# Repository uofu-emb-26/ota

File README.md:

# OTA Firmware Update Project

Reliable A/B firmware update foundation for STM32 with an ESP32 transport bridge.  
Here is the final presentation video showing a demo and explanation of everything in this readme:

## Demo Videos
https://youtu.be/UHACsZe9ke4  
https://youtube.com/shorts/yXXsLTlftgA?feature=share

## Table of Contents
* [Project Overview](#project-overview)
* [System Architecture](#system-architecture)
* [Hardware Interfaces & Wiring](#hardware-interfaces--wiring)
* [Basic Setup Instructions](#basic-setup-instructions)
* [Flowcharts](#flowcharts)
* [Current Implementation Status](#current-implementation-status)
* [Repository Layout](#repository-layout)
* [Authors](#authors)

## Project Overview

### Purpose
Many embedded products are deployed in places where physical reflashing is slow, costly, or impossible. A failed firmware update can also brick a device if there is no recovery path. This project builds a robust over-the-air (OTA) update pipeline for an STM32 platform to solve this problem.

### Functionality
The system utilizes an A/B swap firmware update layout. The design keeps one known-good binary active while writing a new downloaded binary to an inactive slot. This allows updates to be validated before they become permanent. The update download process is concurrent. Main application tasks are not halted while the new binary is fetched.

Key components:
* A custom STM32 bootloader validates candidate app binaries at boot.
* The same application is built twice into Slot A and Slot B with specific binary information.
* OTA update workflow metadata is stored in flash with power-fail-safe writes.
* An ESP32 transport companion delivers update payloads to the STM32 application over UART.

## System Architecture

End-to-end update path:
1. A new firmware binary file is delivered over the network to the ESP32 bridge (stored at https://github.com/anton2uha/OTAfiles).
2. HiveMQ sends a fetch request to the ESP32. The ESP32 downloads the binaries to its local flash.
3. The running STM32 application receives the payload from the ESP32 via UART and writes it to the dormant flash bank.
4. The application marks the dormant slot as pending and reboots.
5. The bootloader validates available slots (integrity, CRC) and selects the boot target with the highest version.
6. The new app image confirms itself after health checks.

### Architecture Diagrams

## Hardware Interfaces & Wiring
### Gerber files and kicad_pcb files can be found in the ``/hardware_design_resources`` dir, for those interested in ordering the hardware to run the OTA.
[//]: # ([PLACEHOLDER: Insert Wiring Diagram Here])

### ESP32 to STM32 UART Pinout
| ESP32 | STM32 |
|---|---|
| GPIO17 (TX) | RX pin (PC5) |
| GPIO16 (RX) | TX pin (PC4) |
| GND | GND |

### STM32 Interfaces
* `UART3`: OTA data path from ESP32 to STM32 (Pins PC4, PC5).
* `UART4`: Debug output path.

### ESP32 Interfaces
* `UART0`: USB serial to receive new programs via PlatformIO.
* `UART2`: Binary transfer path toward STM32 OTA updater.

## Basic Setup Instructions

### 1. ESP32 Bridge Setup
**Requirements:** VS Code with PlatformIO extension, HiveMQ Cloud account (free tier), and a 2.4GHz WiFi network.

1. Configure WiFi credentials in `ota_esp32/src/main.cpp`:
   ```cpp
   const char* ssid = "your_network";
   const char* password = "your_password";
   ```
2. Configure the server URL and MQTT credentials in `ota_esp32/src/main.cpp`:
   ```cpp
   #define MQTT_BROKER "your-cluster.hivemq.cloud"
   #define MQTT_USER   "your_username"
   #define MQTT_PASS   "your_password"
   ```
   Update the IP in `fetchBinary()` and `checkForUpdate()` to point to your hosted binaries.
3. Build and upload using PlatformIO. Ensure the ESP32 device is connected via USB. Note: If using WSL, ensure your user is in the `dialout` group to access `/dev/ttyUSB0`.

### 2. STM32 Firmware Setup
**Requirements:** CMake and ARM GCC toolchain.

1. Navigate to the `OTA` directory.
2. Run the following CMake commands to build the bootloader and the two application slots:
   ```bash
   cmake --preset Debug -B build/Debug
   cmake --build build/Debug --target OTA_bootloader
   cmake --build build/Debug --target OTA_app_a
   cmake --build build/Debug --target OTA_app_b
   ```
3. Flash the generated `.elf` or `.hex` files to the STM32 starting at address `0x08000000` for the bootloader.

## Flowcharts

### Bootloader FSM

### UART ESP32 to STM32 Protocol FSM

## Current Implementation Status

* Implemented A/B flash partitioning and custom bootloader runtime.
* Runtime slot probing with vector checks, manifest checks, CRC checks, and version comparison.
* Shared app source built into two linked images (Slot A and Slot B).
* Power-fail-safe metadata persistence with scratch-page journaling.
* STM32 app-side `UART3` framed OTA receive/write pipeline.
* ESP32 protocol bridge integration.

## Repository Layout

* `OTA`: STM32 firmware workspace.
* `OTA/README.md`: Technical details on file map, flash map, and build/flash details.
* `OTA/PROJECT_HANDOVER.md`: Detailed architecture and roadmap.
* `OTA/ota_esp32`: ESP32 companion workspace.

## Authors

* Sameeran Chandorkar
* Jeffrey Hansen
* Nick Baret
* Anthony Lesik

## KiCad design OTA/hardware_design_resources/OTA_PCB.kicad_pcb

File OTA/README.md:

# OTA STM32 Firmware Workspace

Technical implementation README for the firmware workspace in this directory.

## Table of Contents

- [Overview](#overview)
- [Current Boot Behavior](#current-boot-behavior)
- [Hardware + Interface Plan](#hardware--interface-plan)
- [Memory Layout](#memory-layout)
- [Code Organization](#code-organization)
- [Build and Artifacts](#build-and-artifacts)
- [Flash and Run](#flash-and-run)
- [Status and Roadmap](#status-and-roadmap)

## Overview

This workspace implements a software-managed `A/B OTA` foundation for `STM32F072xB`.

Core components:

- Custom bootloader at flash base.
- Single shared application codebase linked twice (`Slot A`, `Slot B`).
- Per-slot image manifest (`ota_image_info`) embedded in each app image.
- Metadata persistence (`ota_metadata`) for OTA workflow state.

## Current Boot Behavior

Bootloader uses metadata-driven trial/rollback policy. Image validity is still determined from the per-slot manifest.

Decision flow:

1. Probe `Slot A` and `Slot B` (vector table + manifest magic/format/size + CRC).
2. Read OTA metadata (falls back to safe defaults on blank/corrupted flash).
3. If a `pending_slot` is recorded in metadata:
   - If pending slot is invalid or `trial_boot_count >= OTA_MAX_TRIAL_BOOTS` → **rollback** to `confirmed_slot`.
   - Otherwise → increment `trial_boot_count`, persist metadata, **trial boot** pending slot.
4. If no `pending_slot` → boot the recorded `active_slot` if valid.
5. Fallback: version-based runtime selection if active slot is unavailable.
6. If no valid slot found → `BOOT_ERR_NO_VALID_SLOT`, bootloader loops.

Rollback mechanics:
- `ota_mark_slot_pending(slot)` called by the app after writing a new image to the dormant slot.
- App must call `ota_confirm_current_slot()` within `OTA_MAX_TRIAL_BOOTS` boots to promote the slot.
- If not confirmed in time, bootloader rolls back to the previous `confirmed_slot` on next reset.

Implementation references:

- [Core/Src/boot/bootloader_main.c](Core/Src/boot/bootloader_main.c)
- [Core/Src/boot/bootloader.c](Core/Src/boot/bootloader.c)
- [Core/Inc/common/ota_image_info.h](Core/Inc/common/ota_image_info.h)

## Hardware + Interface Plan

### STM32

- `UART3`: planned OTA payload ingress from ESP32 updater.
- `UART4`: debug output path.

### ESP32 companion

- `UART0`: planned binary transfer path toward STM32 app updater.
- `UART2`: planned debug output path.

Companion workspace:

- [ota_esp32](ota_esp32)

## Memory Layout

| Region | Start | End | Size |
|---|---|---|---|
| Bootloader | `0x08000000` | `0x08003FFF` | `16 KB` |
| Slot A | `0x08004000` | `0x080117FF` | `54 KB` |
| Slot B | `0x08011800` | `0x0801EFFF` | `54 KB` |
| Scratch | `0x0801F000` | `0x0801F7FF` | `2 KB` |
| Metadata | `0x0801F800` | `0x0801FFFF` | `2 KB` |

RAM note:

- Vector mirror reserved at `0x20000000` to `0x200000BF`.
- App linker scripts place RAM start at `0x20000100`.

Relevant definitions:

- [Core/Inc/boot/ota_config.h](Core/Inc/boot/ota_config.h)
- [STM32F072_BOOTLOADER.ld](STM32F072_BOOTLOADER.ld)
- [STM32F072_APP_A.ld](STM32F072_APP_A.ld)
- [STM32F072_APP_B.ld](STM32F072_APP_B.ld)

## Code Organization

### Bootloader

- [Core/Inc/boot/bootloader.h](Core/Inc/boot/bootloader.h): bootloader API.
- [Core/Src/boot/bootloader.c](Core/Src/boot/bootloader.c): slot probe, validation, selection, jump.
- [Core/Src/boot/bootloader_main.c](Core/Src/boot/bootloader_main.c): bootloader entrypoint.
- [Core/Src/boot/bootloader_it.c](Core/Src/boot/bootloader_it.c): bootloader interrupt handlers.

### Metadata + workflow state

- [Core/Inc/boot/ota_metadata.h](Core/Inc/boot/ota_metadata.h): metadata layout and API.
- [Core/Src/common/ota_metadata.c](Core/Src/common/ota_metadata.c): CRC, scratch-journal read/write, confirm/pending APIs.

### App image manifest + helpers

- [Core/Inc/common/ota_image_info.h](Core/Inc/common/ota_image_info.h)
- [Core/Src/common/ota_image_info.c](Core/Src/common/ota_image_info.c)
- [Core/Inc/common/ota_app_helper.h](Core/Inc/common/ota_app_helper.h)

### Flash programming abstraction

- [Core/Inc/common/flash_update.h](Core/Inc/common/flash_update.h)
- [Core/Src/common/flash_update.c](Core/Src/common/flash_update.c)

### App entry

- [Core/Src/app/main.c](Core/Src/app/main.c): startup sequence and `ota_confirm_current_slot()` call.

## Build and Artifacts

Primary targets:

- `OTA_bootloader`
- `OTA_app_a`
- `OTA_app_b`

Build commands:

```bash
cmake --preset Debug -B build/Debug
cmake --build build/Debug --target OTA_bootloader
cmake --build build/Debug --target OTA_app_a
cmake --build build/Debug --target OTA_app_b
```

Generated outputs:

- `*.elf`: debug + programming input.
- `*.bin`: raw image payload.
- `*.hex`: address-aware image.
- `*.map`: memory usage map.

Build configuration and post-build tools:

- [CMakeLists.txt](CMakeLists.txt)
- [tools/ota_patch_image_crc.py](tools/ota_patch_image_crc.py)

## Flash and Run

Workspace tasks include:

- `Build All Targets`
- `Flash Bootloader`
- `Flash App A`
- `Flash App B`
- `Flash All Targets`
- `Erase Flash`

Manual command references:

- [flash_commands.txt](flash_commands.txt)

## Status and Roadmap

Current implementation and milestones are tracked in:

- [PROJECT_HANDOVER.md](PROJECT_HANDOVER.md)

Near-term work:

1. Complete app-side `UART3` receive/write pipeline.
2. Complete dormant-slot update state machine.
3. Re-enable metadata-driven trial/rollback policy in bootloader.
4. Add stronger recovery UX for no-valid-slot cases.
5. Add authenticity and anti-rollback security features.

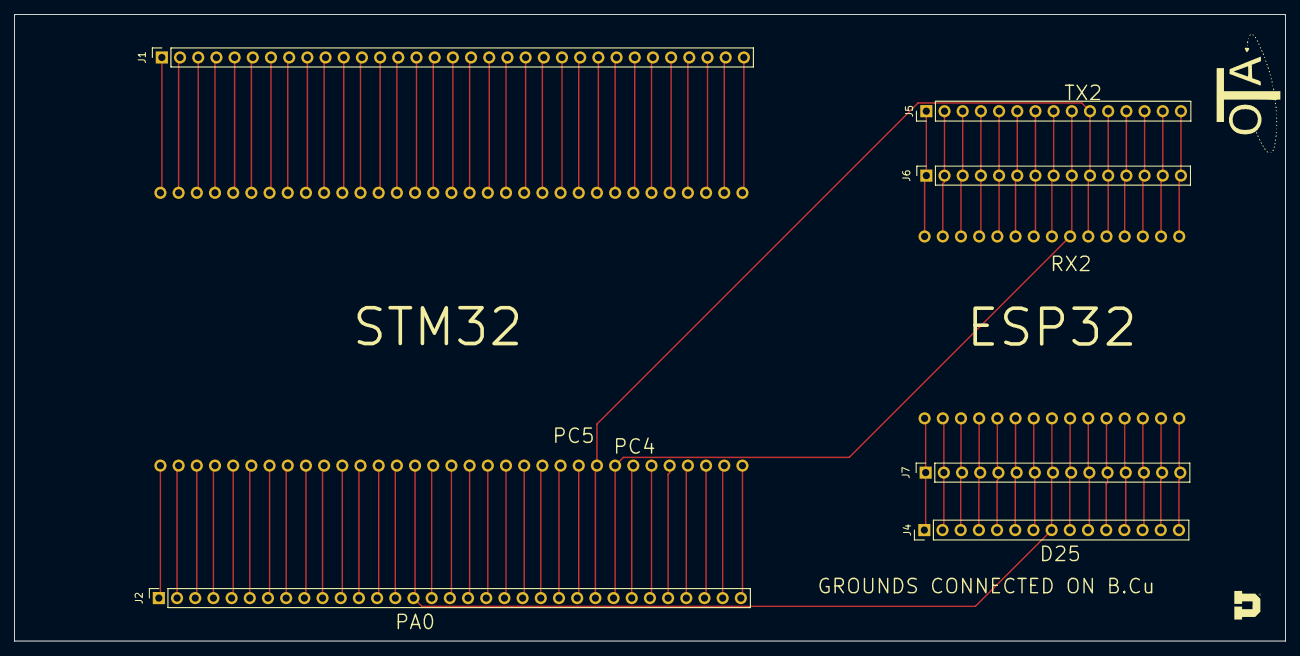
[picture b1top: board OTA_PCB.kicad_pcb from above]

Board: 2 copper layers, 177.5 x 87.5 mm, 8 parts (0 on the bottom side), 90 nets.

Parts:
ESP32: Untitled
J1, J2: Conn_01x33_Socket; PinSocket_1x33_P2.54mm_Vertical
J4, J5: Conn_01x15_Pin; PinHeader_1x15_P2.54mm_Vertical
J6, J7: Conn_01x15_Socket; PinSocket_1x15_P2.54mm_Vertical
STM32: stm32F072B

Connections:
GND: ESP32.14 (GND), ESP32.29 (GND), J1.33, J2.33, J4.14, J5.14, J6.14, J7.14, STM32.P1_33 (GND), STM32.P2_33 (GND)
unnamed: J1.1, STM32.P2_1 (5V)
unnamed: J1.2, STM32.P2_2 (GND)
unnamed: J1.3, STM32.P2_3 (PB9)
unnamed: J1.4, STM32.P2_4 (PB8)
unnamed: J1.5, STM32.P2_5 (VDD)
unnamed: J1.6, STM32.P2_6 (BOOT0)
unnamed: J1.7, STM32.P2_7 (PB7)
unnamed: J1.8, STM32.P2_8 (PB6)
unnamed: J1.9, STM32.P2_9 (PB5)
unnamed: J1.10, STM32.P2_10 (PB4)
unnamed: J1.11, STM32.P2_11 (PB3)
unnamed: J1.12, STM32.P2_12 (PD2)
unnamed: J1.13, STM32.P2_13 (PC12)
unnamed: J1.14, STM32.P2_14 (PC11)
unnamed: J1.15, STM32.P2_15 (PC10)
unnamed: J1.16, STM32.P2_16 (PA15)
unnamed: J1.17, STM32.P2_17 (PA14)
unnamed: J1.18, STM32.P2_18 (VDDIO2)
unnamed: J1.19, STM32.P2_19 (VDDA)
unnamed: J1.20, STM32.P2_20 (PA13)
unnamed: J1.21, STM32.P2_21 (PA12)
unnamed: J1.22, STM32.P2_22 (PA11)
unnamed: J1.23, STM32.P2_23 (PA10)
unnamed: J1.24, STM32.P2_24 (PA9)
unnamed: J1.25, STM32.P2_25 (PA8)
unnamed: J1.26, STM32.P2_26 (PC9)
unnamed: J1.27, STM32.P2_27 (PC8)
unnamed: J1.28, STM32.P2_28 (PC7)
unnamed: J1.29, STM32.P2_29 (PC6)
unnamed: J1.30, STM32.P2_30 (PB15)
unnamed: J1.31, STM32.P2_31 (PB14)
unnamed: J1.32, STM32.P2_32 (PB13)
unnamed: J2.1, STM32.P1_1 (3V)
unnamed: J2.2, STM32.P1_2 (GND)
unnamed: J2.3, STM32.P1_3 (VBAT)
unnamed: J2.4, STM32.P1_4 (PC13)
unnamed: J2.5, STM32.P1_5 (PC14)
unnamed: J2.6, STM32.P1_6 (PC15)
unnamed: J2.7, STM32.P1_7 (PF0)
unnamed: J2.8, STM32.P1_8 (PF1)
unnamed: J2.9, STM32.P1_9 (GND)
unnamed: J2.10, STM32.P1_10 (NRST)
unnamed: J2.11, STM32.P1_11 (PC0)
unnamed: J2.12, STM32.P1_12 (PC1)
unnamed: J2.13, STM32.P1_13 (PC2)
unnamed: J2.14, STM32.P1_14 (PC3)
unnamed: ESP32.8 (D25), J2.15, J4.8, J7.8, STM32.P1_15 (PA0)
unnamed: J2.16, STM32.P1_16 (PA1)
unnamed: J2.17, STM32.P1_17 (PA2)
unnamed: J2.18, STM32.P1_18 (PA3)
unnamed: J2.19, STM32.P1_19 (GND)
unnamed: J2.20, STM32.P1_20 (VDD)
unnamed: J2.21, STM32.P1_21 (PA4)
unnamed: J2.22, STM32.P1_22 (PA5)
unnamed: J2.23, STM32.P1_23 (PA6)
unnamed: J2.24, STM32.P1_24 (PA7)
unnamed: ESP32.25 (RX2), J2.25, J5.10, J6.10, STM32.P1_25 (PC4)
unnamed: ESP32.24 (TX2), J2.26, J5.9, J6.9, STM32.P1_26 (PC5)
unnamed: J2.27, STM32.P1_27 (PB0)
unnamed: J2.28, STM32.P1_28 (PB1)
unnamed: J2.29, STM32.P1_29 (PB2)
unnamed: J2.30, STM32.P1_30 (PB10)
unnamed: J2.31, STM32.P1_31 (PB11)
unnamed: J2.32, STM32.P1_32 (PB12)
unnamed: ESP32.1 (EN), J4.1, J7.1
unnamed: ESP32.2 (VP), J4.2, J7.2
unnamed: ESP32.3 (VN), J4.3, J7.3
unnamed: ESP32.4 (D34), J4.4, J7.4
unnamed: ESP32.5 (D35), J4.5, J7.5
unnamed: ESP32.6 (D32), J4.6, J7.6
unnamed: ESP32.7 (D33), J4.7, J7.7
unnamed: ESP32.9 (D26), J4.9, J7.9
unnamed: ESP32.10 (D27), J4.10, J7.10
unnamed: ESP32.11 (D14), J4.11, J7.11
unnamed: ESP32.12 (D12), J4.12, J7.12
unnamed: ESP32.13 (D13), J4.13, J7.13
unnamed: ESP32.15 (VIN), J4.15, J7.15
unnamed: ESP32.16 (D23), J5.1, J6.1
unnamed: ESP32.17 (D22), J5.2, J6.2
unnamed: ESP32.18 (TX0), J5.3, J6.3
unnamed: ESP32.19 (RX0), J5.4, J6.4
unnamed: ESP32.20 (D21), J5.5, J6.5
unnamed: ESP32.21 (D19), J5.6, J6.6
unnamed: ESP32.22 (D18), J5.7, J6.7
unnamed: ESP32.23 (D5), J5.8, J6.8
unnamed: ESP32.26 (D4), J5.11, J6.11
unnamed: ESP32.27 (D2), J5.12, J6.12
unnamed: ESP32.28 (D15), J5.13, J6.13
unnamed: ESP32.30 (3V3), J5.15, J6.15

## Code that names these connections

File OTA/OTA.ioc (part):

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Mcu.Name=STM32F072R(8-B)Tx
Mcu.Package=LQFP64
Mcu.UserName=STM32F072RBTx
PA0.GPIOParameters=GPIO_Label,GPIO_ModeDefaultEXTI
PA0.GPIO_Label=B1 [Blue PushButton]
PA0.GPIO_ModeDefaultEXTI=GPIO_MODE_EVT_RISING
PA0.Signal=GPXTI0
PA1.Mode=Asynchronous
PA1.Signal=USART4_RX
PA11.GPIOParameters=GPIO_Label
PA11.GPIO_Label=USBF4_DM
PA11.Mode=Device
PA11.Signal=USB_DM
PA12.GPIOParameters=GPIO_Label
PA12.GPIO_Label=USBF4_DP
PA12.Mode=Device
PA12.Signal=USB_DP
PA13.GPIOParameters=GPIO_Label
PA13.GPIO_Label=SWDIO
PA13.Mode=Serial_Wire
PA13.Signal=SYS_SWDIO
PA14.GPIOParameters=GPIO_Label
PA14.GPIO_Label=SWCLK
PA14.Mode=Serial_Wire
PA14.Signal=SYS_SWCLK
PA2.Mode=G1_IO3-Channel
PA2.Signal=TSC_G1_IO3
PA3.Mode=G1_IO4-Sampling
PA3.Signal=TSC_G1_IO4
PA6.Mode=G2_IO3-Channel
PA6.Signal=TSC_G2_IO3
PA7.Mode=G2_IO4-Sampling
PA7.Signal=TSC_G2_IO4
PB0.Mode=G3_IO2-Channel
PB0.Signal=TSC_G3_IO2
PB1.Mode=G3_IO3-Sampling
PB1.Signal=TSC_G3_IO3
PB10.GPIOParameters=GPIO_Label,GPIO_Pu
PB10.GPIO_Label=I2C2_SCL[EXT/RF-E2P_SCL]
PB10.GPIO_Pu=GPIO_PULLUP
PB10.Mode=I2C
PB10.Signal=I2C2_SCL
PB11.GPIOParameters=GPIO_Label,GPIO_Pu
PB11.GPIO_Label=I2C2_SDA[EXT/RF-E2P_SDA]
PB11.GPIO_Pu=GPIO_PULLUP
PB11.Mode=I2C
PB11.Signal=I2C2_SDA
PB13.GPIOParameters=GPIO_Label
PB13.GPIO_Label=SPI2_SCK [L3GD20_SCL/SPC]
PB13.Mode=Full_Duplex_Master
PB13.Signal=SPI2_SCK
PB14.GPIOParameters=GPIO_Label
PB14.GPIO_Label=SPI2_MISO [L3GD20_SDO]
PB14.Mode=Full_Duplex_Master
PB14.Signal=SPI2_MISO
PB15.GPIOParameters=GPIO_Label
PB15.GPIO_Label=SPI2_MOSI [L3GD20_SDA/SDI]
PB15.Mode=Full_Duplex_Master
PB15.Signal=SPI2_MOSI
PC0.GPIOParameters=GPIO_Label
PC0.GPIO_Label=NCS_MEMS_SPI [L3GD20_CS_I2C/SPI]
PC0.Signal=GPIO_Output
PC1.GPIOParameters=GPIO_Label,GPIO_ModeDefaultEXTI
PC1.GPIO_Label=MEMS_INT1 [L3GD20_INT1]
PC1.GPIO_ModeDefaultEXTI=GPIO_MODE_EVT_RISING
PC1.Signal=GPXTI1
PC10.Mode=Asynchronous
PC10.Signal=USART4_TX
PC2.GPIOParameters=GPIO_Label,GPIO_ModeDefaultEXTI
PC2.GPIO_Label=MEMS_INT2 [L3GD20_INT2]
PC2.GPIO_ModeDefaultEXTI=GPIO_MODE_EVT_RISING
PC2.Signal=GPXTI2
PC5.GPIOParameters=GPIO_Label
PC5.GPIO_Label=EXT_RESET [EXT/RF-E2P_EXT_RESET]
PC5.Signal=GPIO_Output
PC6.GPIOParameters=GPIO_Label
PC6.GPIO_Label=LD3 [Red Led]
PC6.Signal=GPIO_Output
PC7.GPIOParameters=GPIO_Label
PC7.GPIO_Label=LD6 [Blue Led]
PC7.Signal=GPIO_Output
PC8.GPIOParameters=GPIO_Label
PC8.GPIO_Label=LD4 [Orange Led]
PC8.Signal=GPIO_Output
PC9.GPIOParameters=GPIO_Label
PC9.GPIO_Label=LD5 [GReen Led]
PC9.Signal=GPIO_Output
RCC.SYSCLKFreq_VALUE=48000000
RCC.SYSCLKSource=RCC_SYSCLKSOURCE_PLLCLK
board=STM32F072B-DISCO
boardIOC=true

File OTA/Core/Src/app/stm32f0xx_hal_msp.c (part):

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
    __HAL_RCC_GPIOB_CLK_ENABLE();
    /**I2C2 GPIO Configuration
    PB10     ------> I2C2_SCL
    PB11     ------> I2C2_SDA
    */
    GPIO_InitStruct.Pin = I2C2_SCL_Pin|I2C2_SDA_Pin;
    GPIO_InitStruct.Mode = GPIO_MODE_AF_OD;
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    __HAL_RCC_I2C2_CLK_DISABLE();

    /**I2C2 GPIO Configuration
    PB10     ------> I2C2_SCL
    PB11     ------> I2C2_SDA
    */
    HAL_GPIO_DeInit(I2C2_SCL_GPIO_Port, I2C2_SCL_Pin);

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
    __HAL_RCC_GPIOB_CLK_ENABLE();
    /**SPI2 GPIO Configuration
    PB13     ------> SPI2_SCK
    PB14     ------> SPI2_MISO
    PB15     ------> SPI2_MOSI
    */
    GPIO_InitStruct.Pin = SPI2_SCK_Pin|SPI2_MISO_Pin|SPI2_MOSI_Pin;
    GPIO_InitStruct.Mode = GPIO_MODE_AF_PP;
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    __HAL_RCC_SPI2_CLK_DISABLE();

    /**SPI2 GPIO Configuration
    PB13     ------> SPI2_SCK
    PB14     ------> SPI2_MISO
    PB15     ------> SPI2_MOSI
    */
    HAL_GPIO_DeInit(GPIOB, SPI2_SCK_Pin|SPI2_MISO_Pin|SPI2_MOSI_Pin);

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    __HAL_RCC_GPIOA_CLK_ENABLE();
    __HAL_RCC_GPIOB_CLK_ENABLE();
    /**TSC GPIO Configuration
    PA2     ------> TSC_G1_IO3
    PA3     ------> TSC_G1_IO4
    PA6     ------> TSC_G2_IO3
    PA7     ------> TSC_G2_IO4
    PB0     ------> TSC_G3_IO2
    PB1     ------> TSC_G3_IO3
    */
    GPIO_InitStruct.Pin = GPIO_PIN_2|GPIO_PIN_6;
    GPIO_InitStruct.Mode = GPIO_MODE_AF_PP;
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    __HAL_RCC_TSC_CLK_DISABLE();

    /**TSC GPIO Configuration
    PA2     ------> TSC_G1_IO3
    PA3     ------> TSC_G1_IO4
    PA6     ------> TSC_G2_IO3
    PA7     ------> TSC_G2_IO4
    PB0     ------> TSC_G3_IO2
    PB1     ------> TSC_G3_IO3
    */
    HAL_GPIO_DeInit(GPIOA, GPIO_PIN_2|GPIO_PIN_3|GPIO_PIN_6|GPIO_PIN_7);

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  //   __HAL_RCC_GPIOA_CLK_ENABLE();
  //   __HAL_RCC_GPIOC_CLK_ENABLE();
  //   /**USART4 GPIO Configuration
  //   PA1     ------> USART4_RX
  //   PC10     ------> USART4_TX
  //   */
  //   GPIO_InitStruct.Pin = GPIO_PIN_1;
  //   GPIO_InitStruct.Mode = GPIO_MODE_AF_PP;
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
    __HAL_RCC_GPIOC_CLK_ENABLE();
    /**USART3 GPIO Configuration
    PC4     ------> USART3_TX
    PC11     ------> USART3_RX
    */
    GPIO_InitStruct.Pin = GPIO_PIN_4|GPIO_PIN_11;
    GPIO_InitStruct.Mode = GPIO_MODE_AF_PP;
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    __HAL_RCC_USART4_CLK_DISABLE();

    /**USART4 GPIO Configuration
    PA1     ------> USART4_RX
    PC10     ------> USART4_TX
    */
    HAL_GPIO_DeInit(GPIOA, GPIO_PIN_1);

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    __HAL_RCC_USART3_CLK_DISABLE();

    /**USART3 GPIO Configuration
    PC4     ------> USART3_TX
    PC11     ------> USART3_RX
    */
    HAL_GPIO_DeInit(GPIOC, GPIO_PIN_4|GPIO_PIN_11);

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
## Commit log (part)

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2026-03-20 Update README to include project title and author
2026-03-21 Anthony first commit
2026-03-21 Enhance README with OTA system details and authors
    Added detailed description of the OTA update system and authors.
2026-03-21 Added Jeffrey Hansen to Authors
2026-03-21 fixed lines in readme
2026-03-27 implemented setup from cube32 allowing direct flash with debugging from debug interface
2026-03-27 started adding flash functions
2026-03-27 a few more flash r/w functions
2026-03-27 added some comments
2026-03-27 added comments on page remove, and check for BSY bit at start of routine ffor page erase
2026-03-27 added uart
2026-03-27 functional write to flash from button push
2026-03-28 stash
2026-04-03 commiting Jeff_temp to main
2026-04-03 Update to jeff's build
2026-04-03 added crc and usart4
2026-04-03 added full setup of CRC and USART4
2026-04-03 more fix
2026-04-04 Introduced linker scripts for application slots A and B, and bootloader.
2026-04-04 make the main branch compilable
2026-04-09 Code restructuring for simplified file management
2026-04-09 added platformIO project for ESP32 on Arduino framework
2026-04-09 add WSL upload fix guide for ESP32 in README
2026-04-10 added usart3 and 4 stuff - some sort of bug
2026-04-10 Enable interrupts just after jumping to application code
2026-04-11 added usart stuff from lab - not working on long strings
2026-04-16 Implement LED control and UART debug functionality; update metadata structure and bootloader logic
2026-04-17 got wifi working and started setting up fetch from server
2026-04-17 added a comment for clarity
2026-04-17 added starting arduino UART code in esp32 dir
2026-04-17 Refactor UART debug implementation to use USART4; update related configurations and clean up code
2026-04-18 added user flash mass erase command
2026-04-18 Implement OTA image info structure and update bootloader logic for slot management; refactor metadata handling and adjust linker scripts for image info placement
2026-04-18 Minor cosmetic changes
2026-04-18 Refactor PROJECT_HANDOVER.md to clarify OTA architecture and current state
2026-04-18 Implement CRC stamping for OTA images, enhance image validation, and add logging for bootloader slot reasons
2026-04-19 added code to read .bin file from server and store it within ESP32
2026-04-19 Updated readme files for better clarity and documentation
2026-04-21 added sending from esp32 to stm32 using uart3 on stm32
2026-04-21 sending up to 250 bytes
2026-04-21 sending 250 bytes
2026-04-24 added code to check for update and added instructions for how to run in readme
2026-04-24 added some macros for easy porting when people run on their machines
2026-04-24 added FSM implementation for esp32 <-> STM32 handshake
2026-04-24 added flash update communication protocol
2026-04-24 addition to flash update
2026-04-24 light cleanup of naming and definitions
2026-04-24 added comments
2026-04-24 removed sensitive stuff
2026-04-24 sensitive info remove
2026-04-24 uart3 added
2026-04-24 starting working on CRC check
2026-04-24 hello
2026-04-25 working crc, merged nick's changes
2026-04-25 removed sensitive info
2026-04-25 added second firmware bank (B) functionality
2026-04-25 replace polling with MQTT triggered updates over HiveMQ
2026-04-25 adding prints for debug and write
2026-04-25 changed types
2026-04-26 updated main.cpp with read buffer flushing before transaction and additional adjustments
2026-04-26 added sensitive_data.h which includes header definitions to store senstive info after adding the file to git ignore a template is being included with this push outside of git ignore
2026-04-26 fixed adding example instead of only actual file that will disapear
2026-04-26 comms workinggit add .git add .git add .git add .
2026-04-26 rem ting
2026-04-26 comms working
2026-04-26 gitingore, error enums added
2026-04-26 fixed?
2026-04-26 maybe working commit?
2026-04-26 merged with commsv1
2026-04-26 update to enter from update being pushed
2026-04-26 refactor: updated MQTT broker definition location
2026-04-26 add src/config.h to .gitignore
2026-04-26 working communication protocol
2026-04-26 remove: delete config.h file containing sensitive information
2026-04-26 fixed byte orientation
2026-04-26 added handshake for region determination and added push button look for update from stm32
2026-04-26 Got button interrupt working
2026-04-27 cleaned up program comments and added non blocking push button functionallity
2026-04-27 Implemented esp32 pushes stm32 button
2026-04-27 Implemented software reset upon successful flashwrite
2026-04-30 readme updates
2026-04-30 Implement metadata-driven trial/rollback policy in bootloader and update documentation
2026-04-30 update readme again
2026-04-30 merged new readme updates from main into this
2026-04-30 adding wiring image
2026-04-30 wiring diagram added to readme
2026-04-30 added hardware files
2026-05-06 add contributor
2026-05-06 add contributor again

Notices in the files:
OTA/Core/Src/app/stm32f0xx_hal_msp.c:
Copyright (c) 2026 STMicroelectronics.
All rights reserved.
This software is licensed under terms that can be found in the LICENSE file
